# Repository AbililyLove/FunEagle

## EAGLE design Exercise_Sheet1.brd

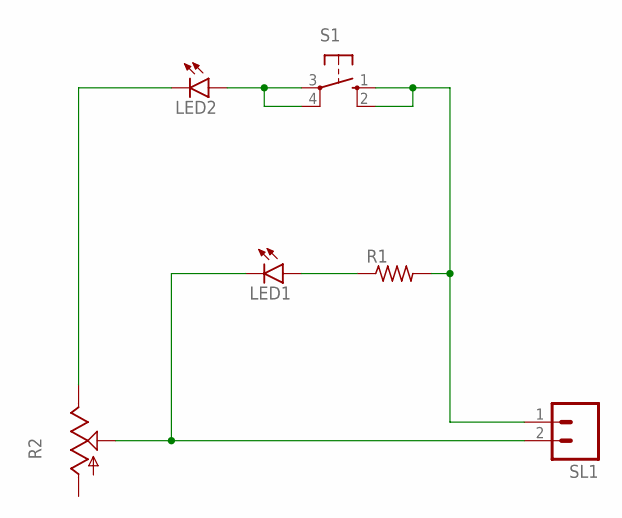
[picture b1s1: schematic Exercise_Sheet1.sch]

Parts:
LED1, LED2: LED5MM
R1: R-US_0207/12; 0207/12
R2: TRIM_US-3223G; 3223G
S1: 10-XX; B3F-10XX
SL1: M02; 02P

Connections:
unnamed: LED2.K (C), R2.3 (E)
unnamed: LED2.A, S1.3, S1.4 (P1)
unnamed: R1.2, S1.1 (S), S1.2 (S1), SL1.1
unnamed: LED1.A, R1.1
unnamed: LED1.K (C), R2.2 (S), SL1.2

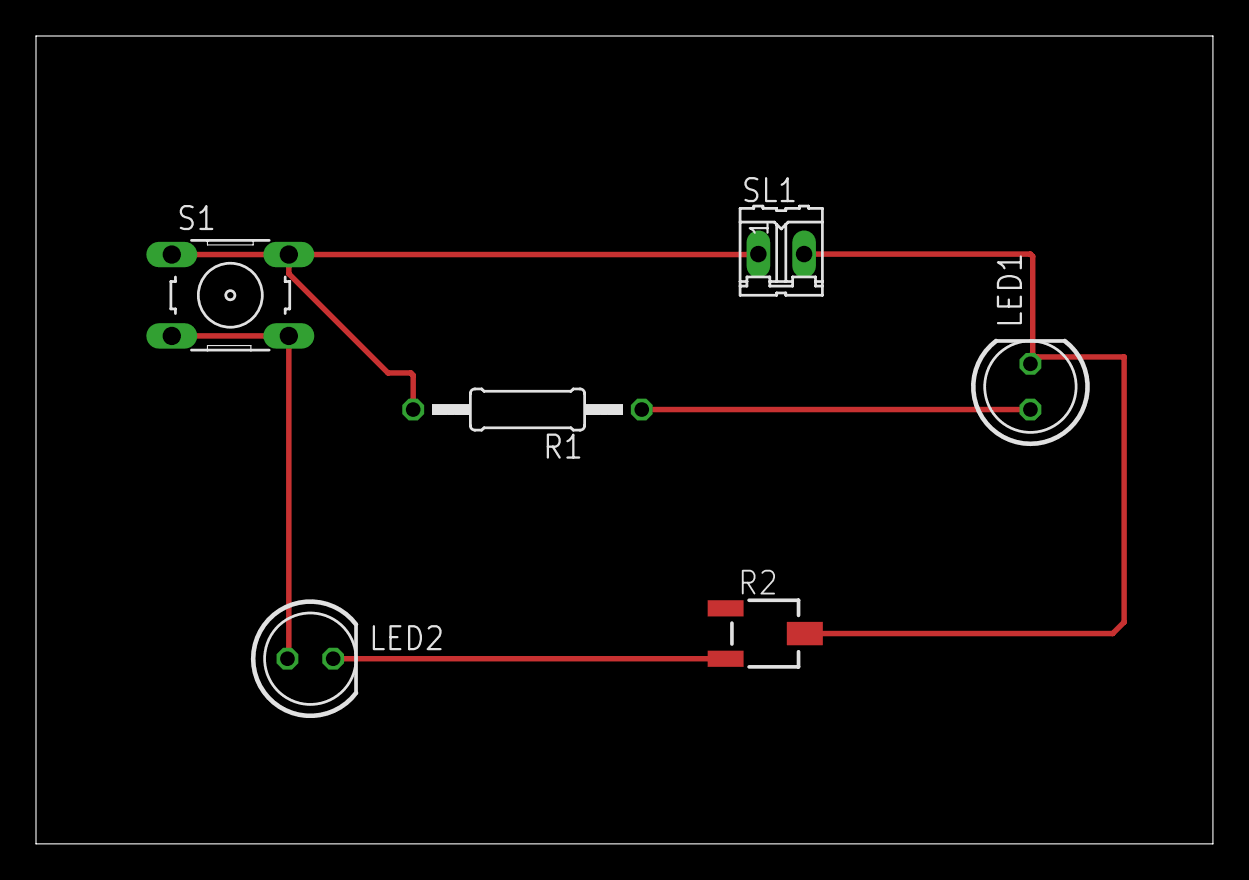
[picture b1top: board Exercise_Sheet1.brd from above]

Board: 2 copper layers, 65.4 x 44.9 mm, 6 parts (0 on the bottom side), 5 nets.
